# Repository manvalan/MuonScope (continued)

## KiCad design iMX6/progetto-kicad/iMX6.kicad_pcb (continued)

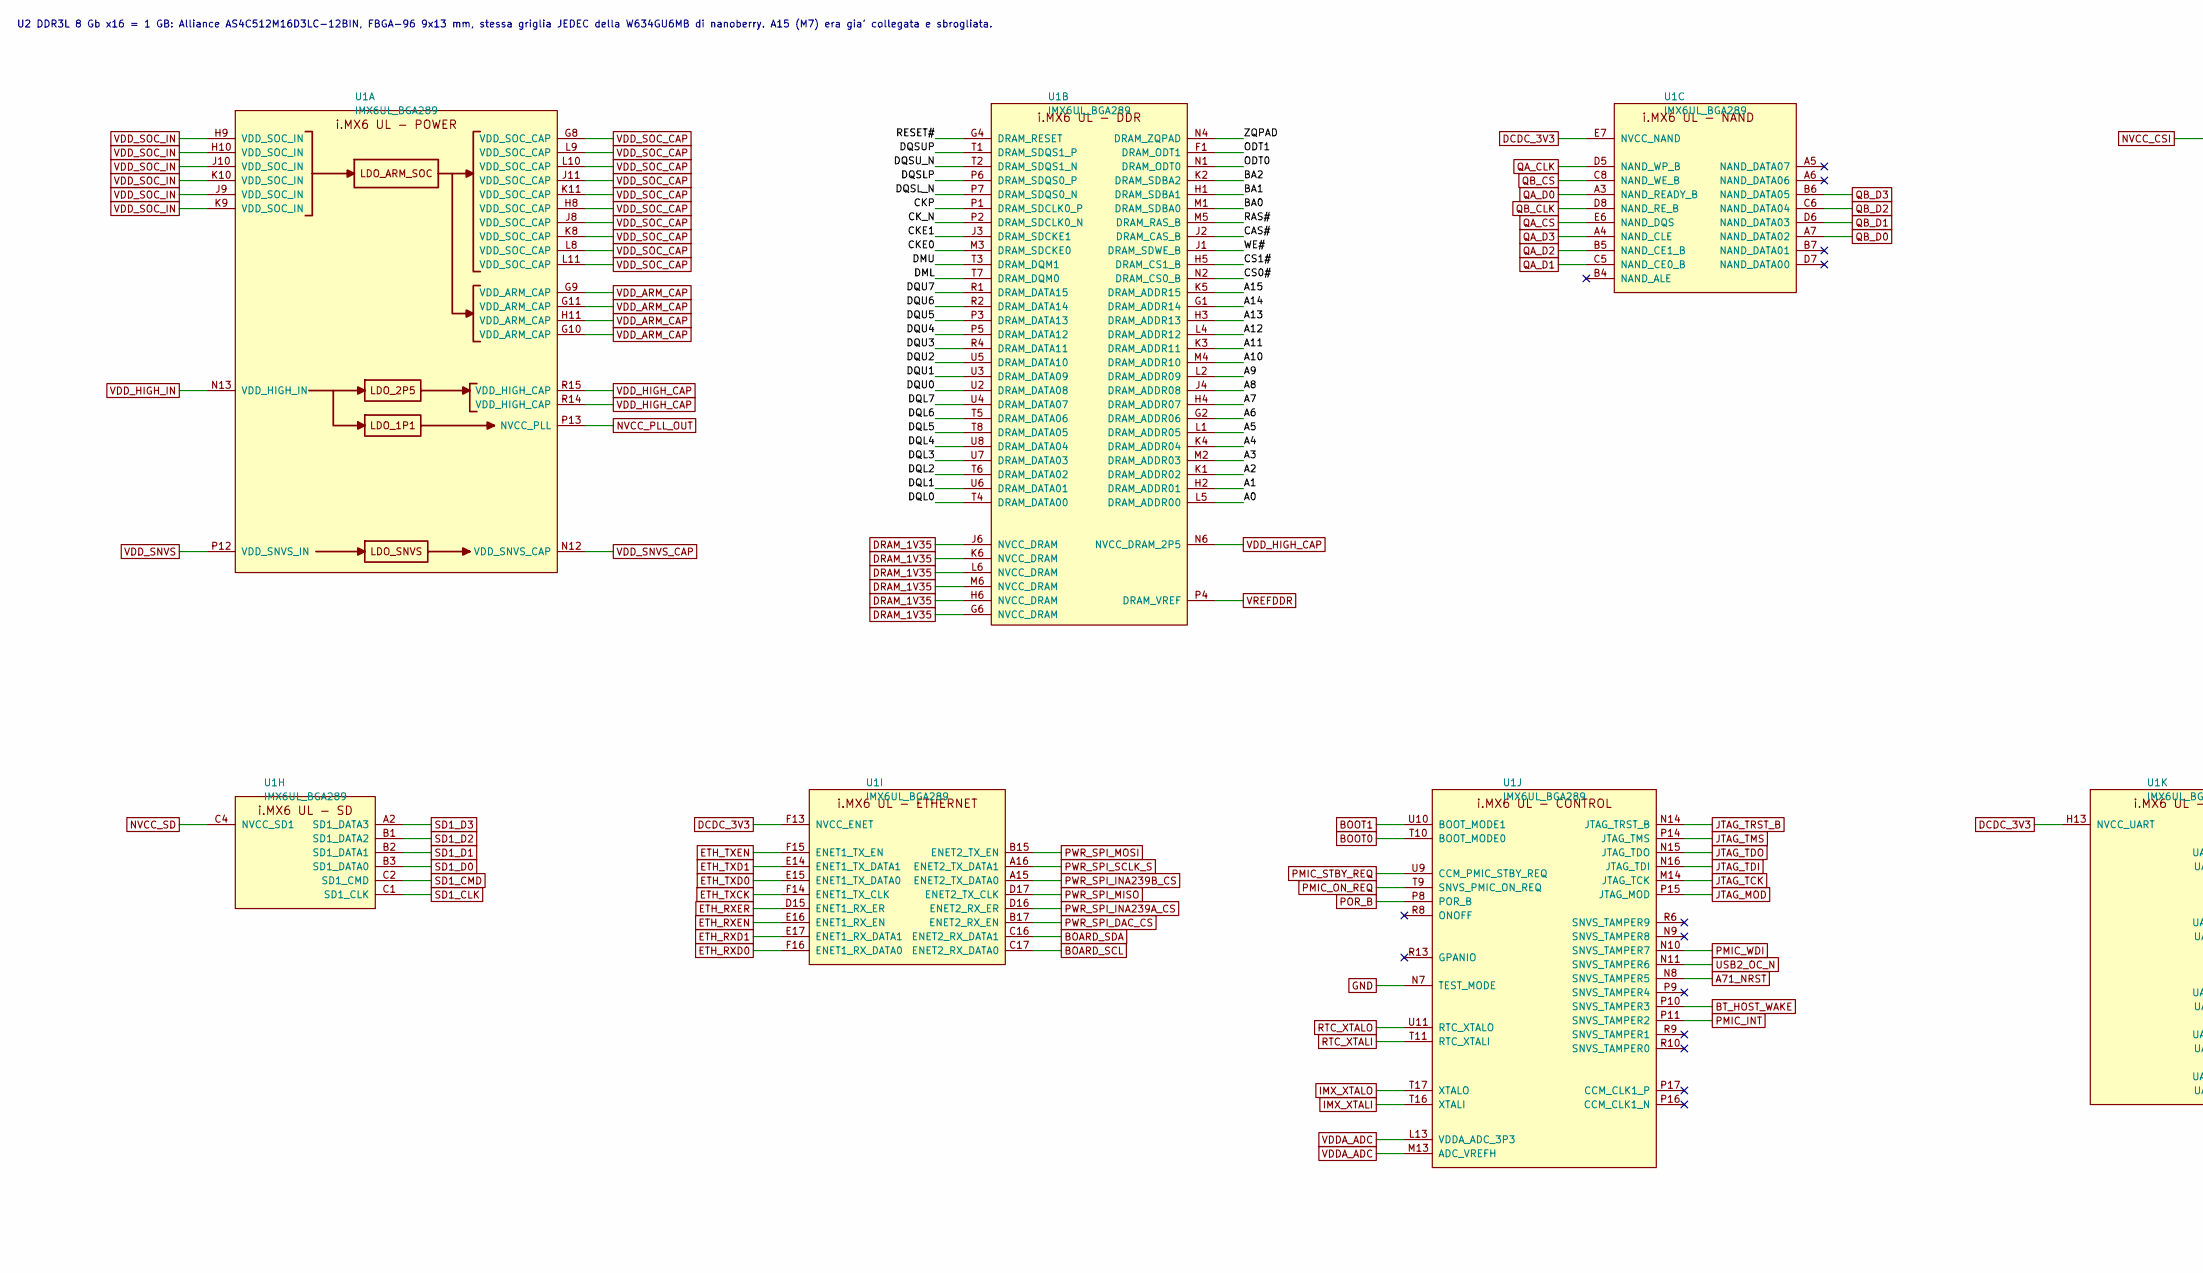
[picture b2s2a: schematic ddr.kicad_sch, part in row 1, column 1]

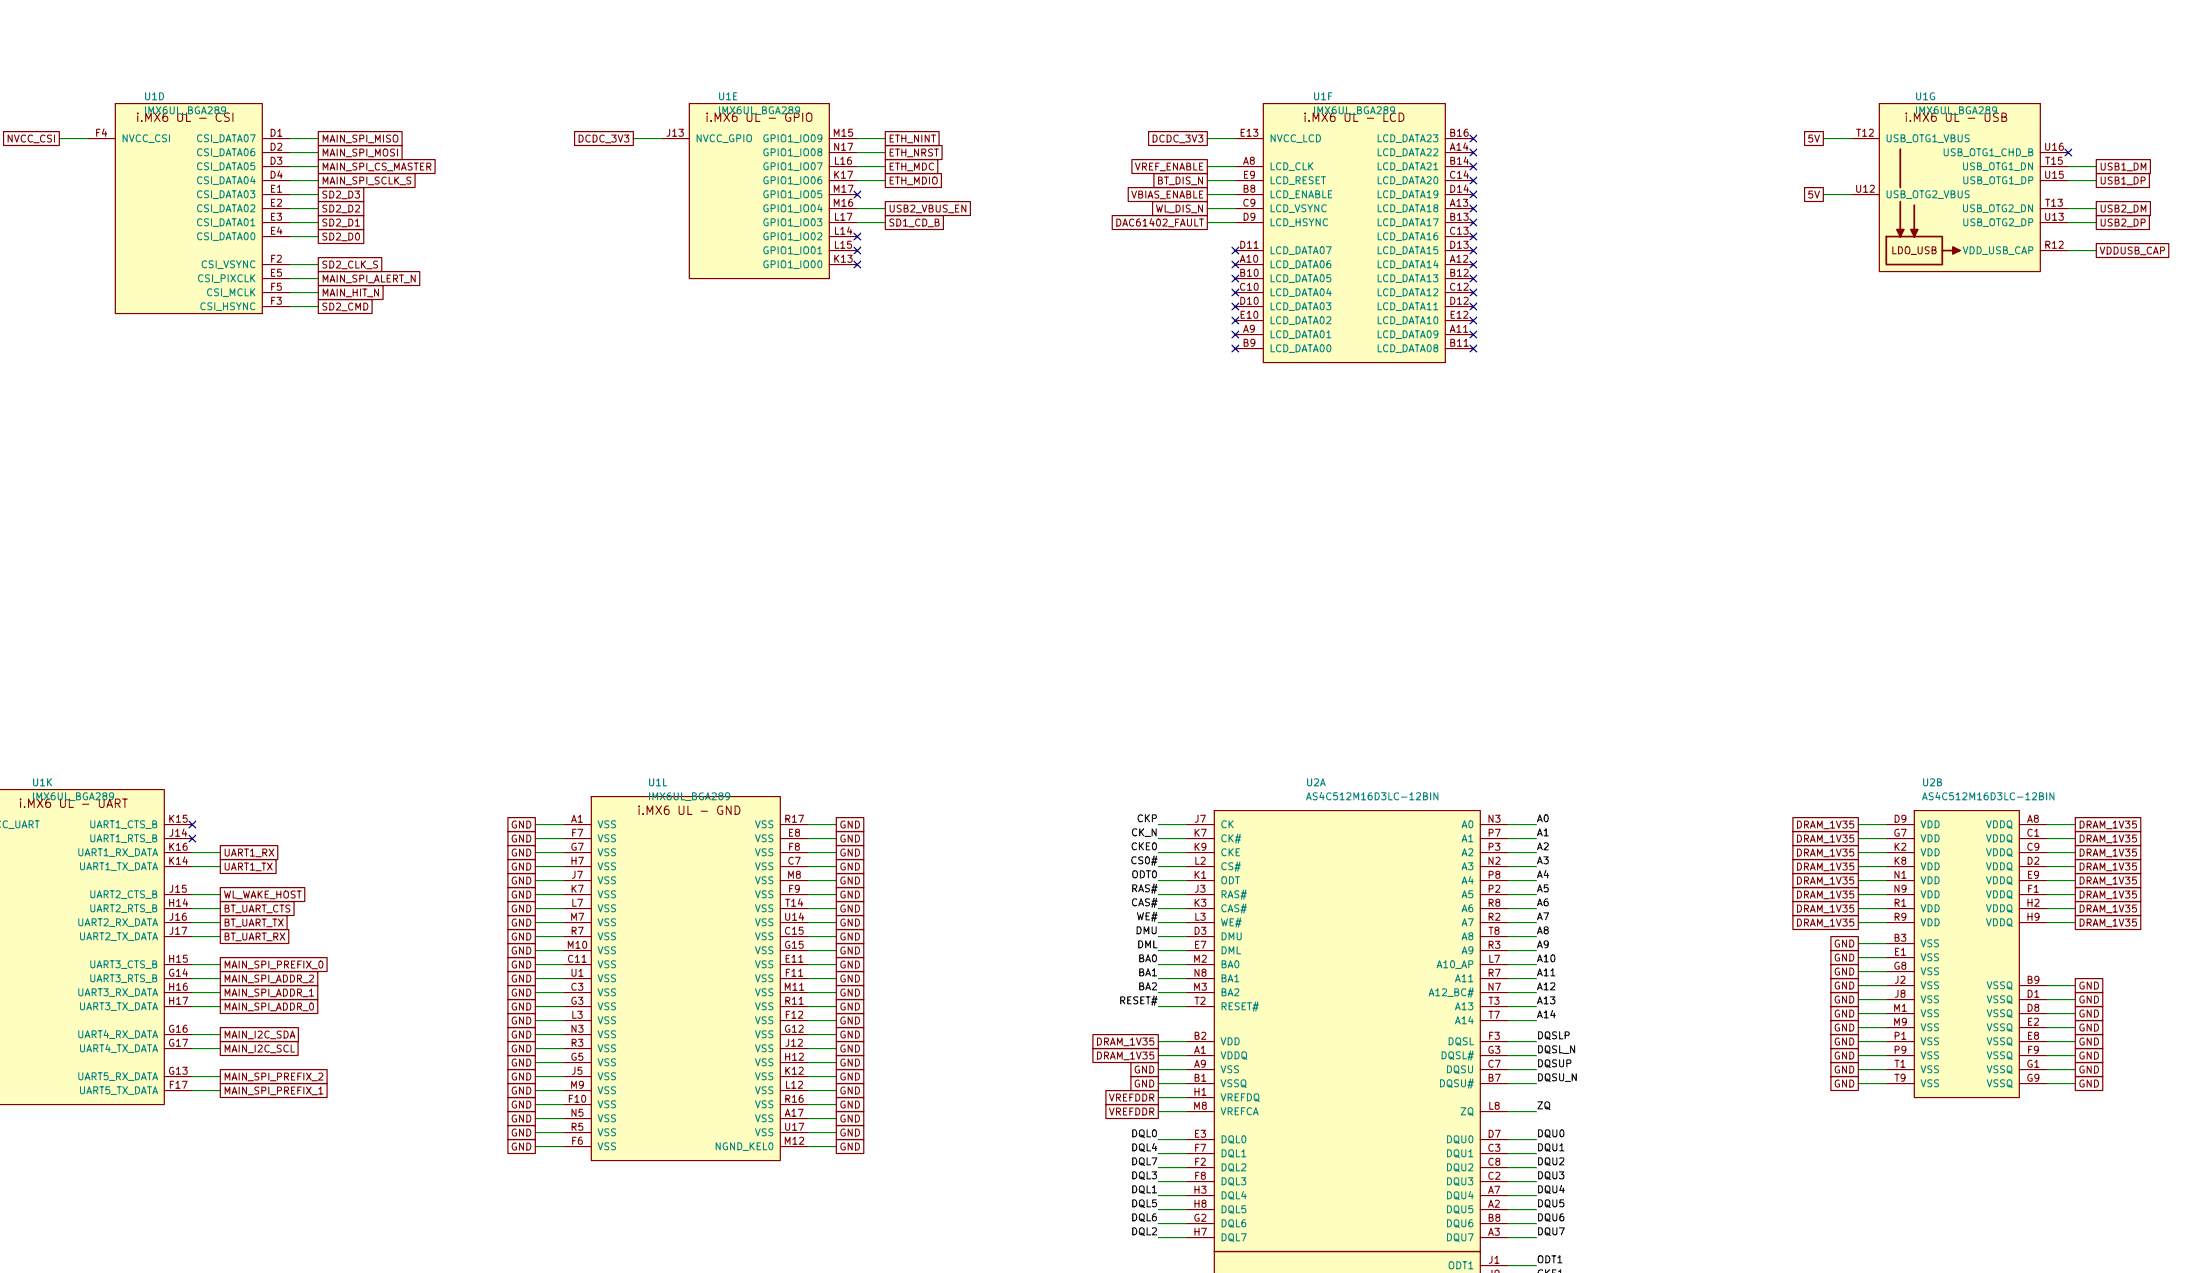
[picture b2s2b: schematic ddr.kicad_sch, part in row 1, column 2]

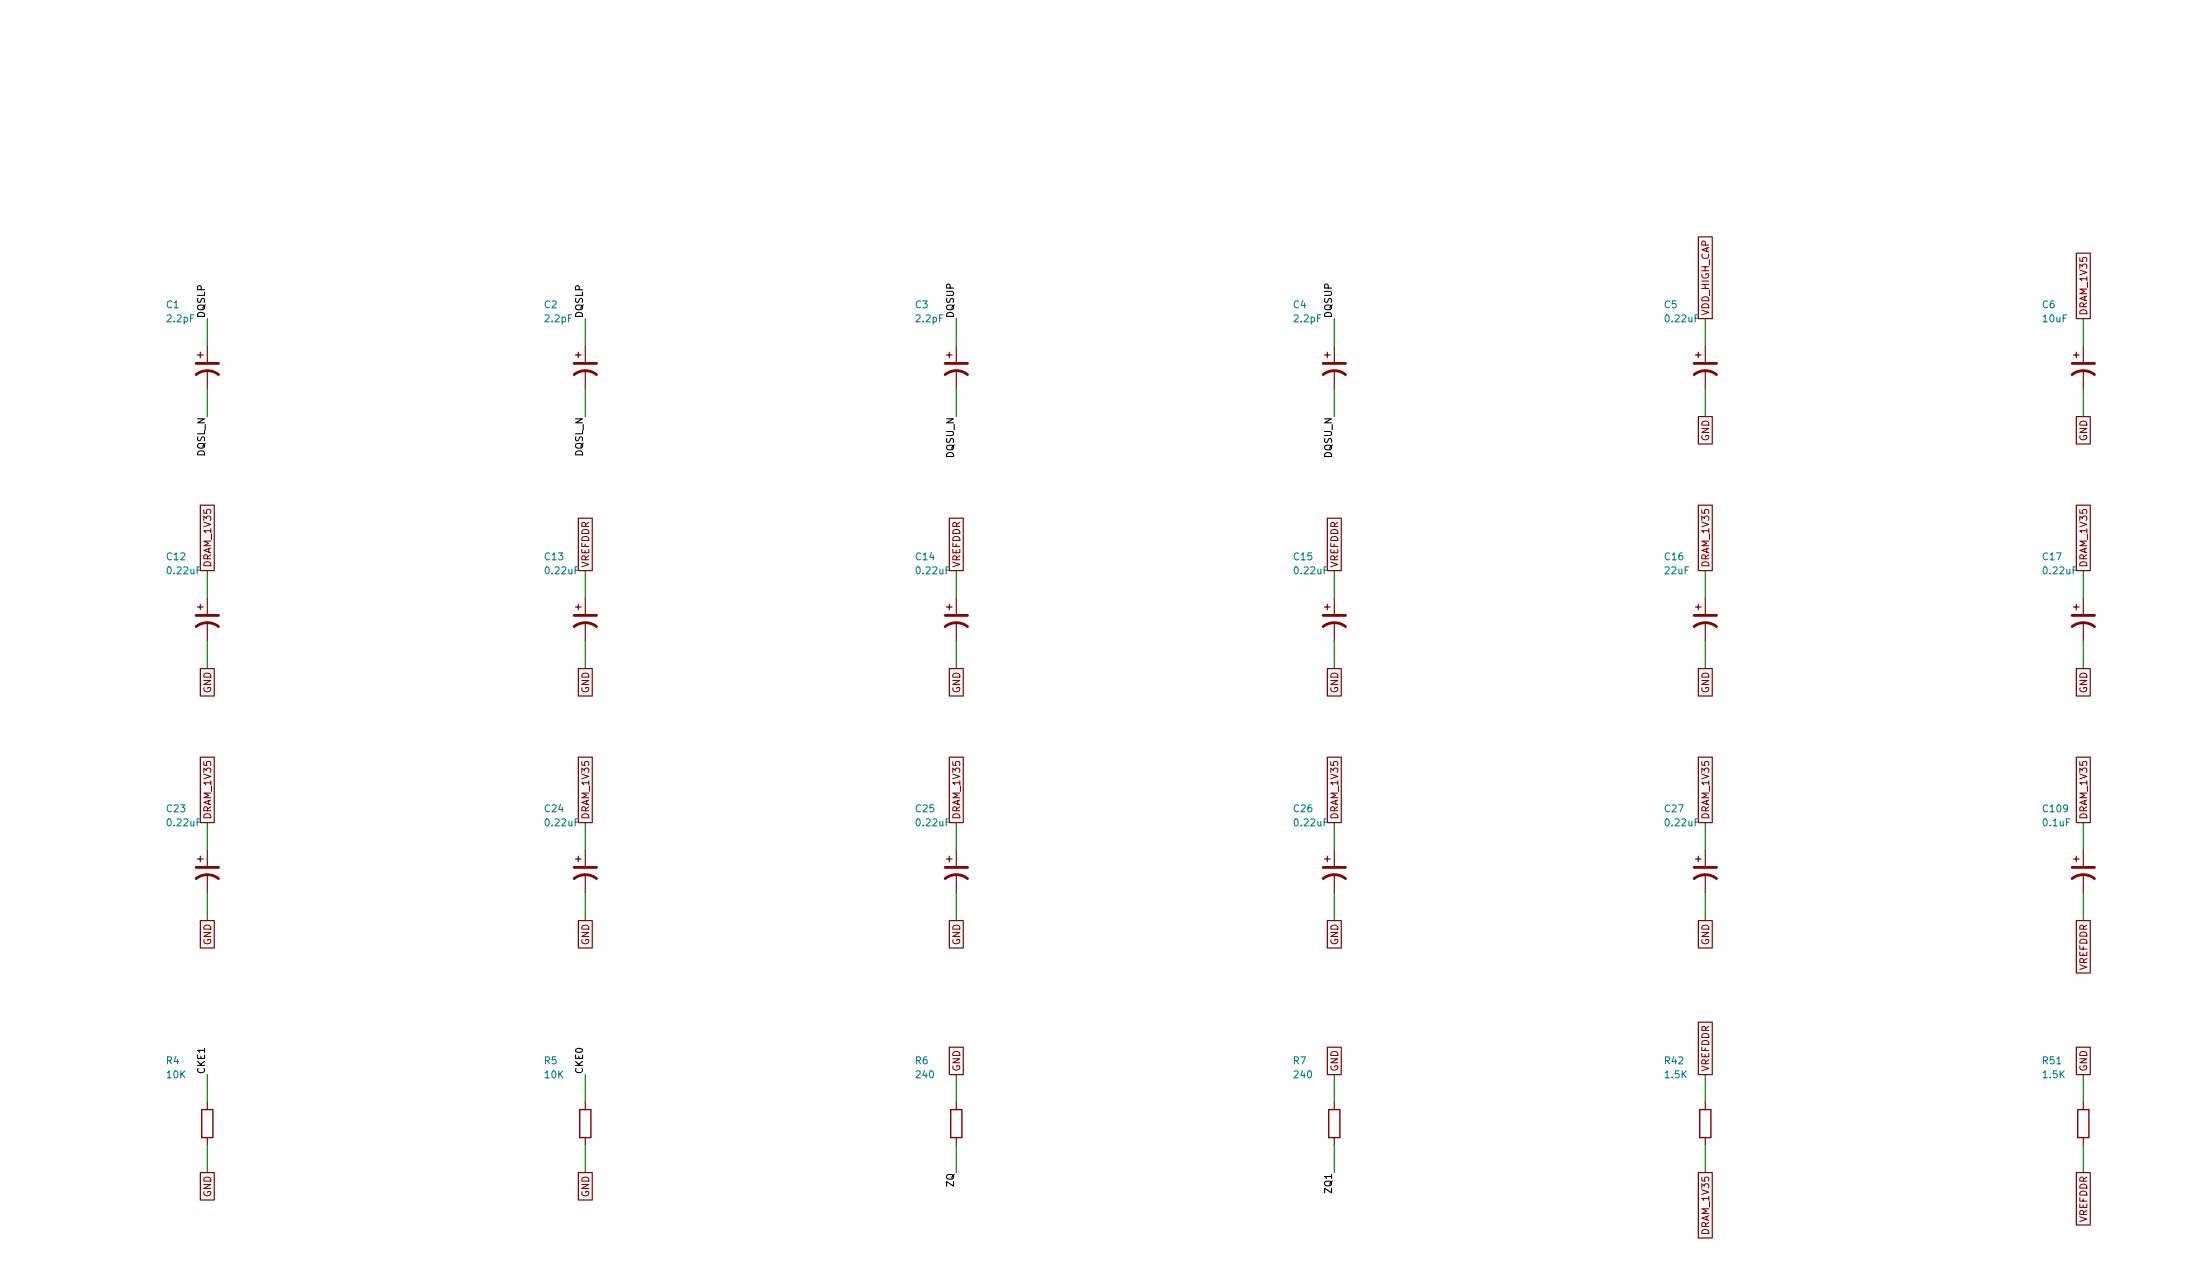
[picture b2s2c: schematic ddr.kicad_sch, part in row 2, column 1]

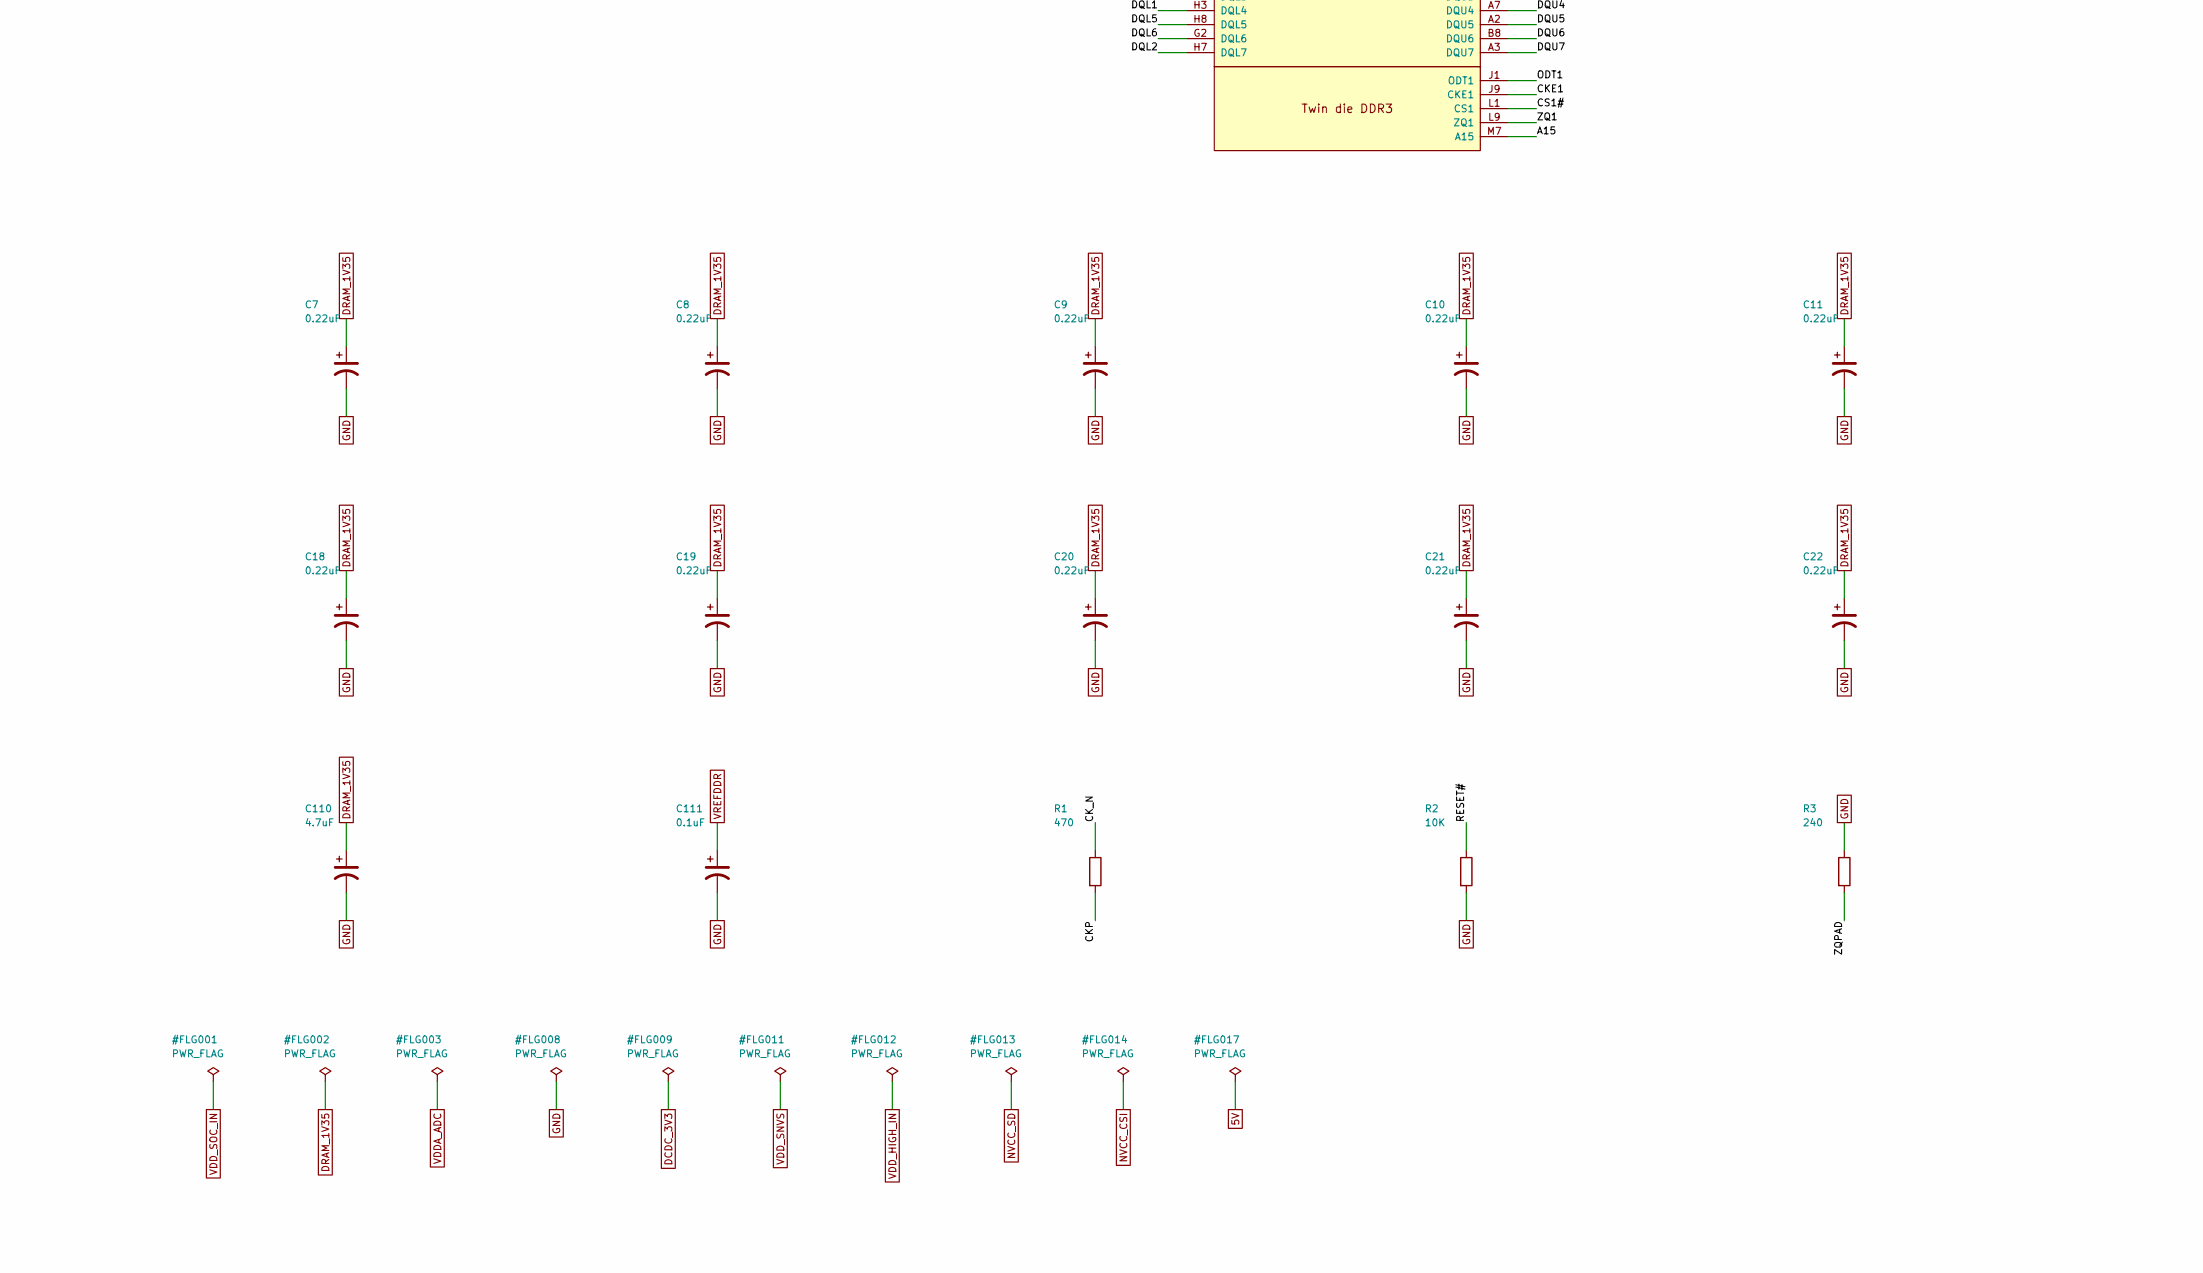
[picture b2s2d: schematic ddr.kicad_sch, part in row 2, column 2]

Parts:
C1, C2, C3, C4: 2.2pF; C_0402_narrow
C5, C7, C8, C9, C10, C11, C12, C13, C14, C15, C17, C18, C19, C20, C21, C22, C23, C24, C25, C26, C27: 0.22uF; C_0402_narrow
C6: 10uF; C_0603_narrow
C16: 22uF; C_0603_narrow
C109, C111: 0.1uF; C_0402_narrow
C110: 4.7uF; C_0402_narrow
R1: 470; R_0402_narrow
R2, R4, R5: 10K; R_0402_narrow
R3, R6, R7: 240; R_0402_narrow
R42, R51: 1.5K; R_0402_narrow
U1: IMX6UL_BGA289
U2: AS4C512M16D3LC-12BIN; DDR3_BGA96

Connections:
5V: U1.T12 (USB_OTG1_VBUS), U1.U12 (USB_OTG2_VBUS); also elsewhere on the board
/DDR3L/A0: U1.L5 (DRAM_ADDR00), U2.N3 (A0)
/DDR3L/A1: U1.H2 (DRAM_ADDR01), U2.P7 (A1)
/DDR3L/A2: U1.K1 (DRAM_ADDR02), U2.P3 (A2)
/DDR3L/A3: U1.M2 (DRAM_ADDR03), U2.N2 (A3)
/DDR3L/A4: U1.K4 (DRAM_ADDR04), U2.P8 (A4)
/DDR3L/A5: U1.L1 (DRAM_ADDR05), U2.P2 (A5)
/DDR3L/A6: U1.G2 (DRAM_ADDR06), U2.R8 (A6)
/DDR3L/A7: U1.H4 (DRAM_ADDR07), U2.R2 (A7)
/DDR3L/A8: U1.J4 (DRAM_ADDR08), U2.T8 (A8)
/DDR3L/A9: U1.L2 (DRAM_ADDR09), U2.R3 (A9)
/DDR3L/A10: U1.M4 (DRAM_ADDR10), U2.L7 (A10_AP)
/DDR3L/A11: U1.K3 (DRAM_ADDR11), U2.R7 (A11)
/DDR3L/A12: U1.L4 (DRAM_ADDR12), U2.N7 (A12_BC#)
/DDR3L/A13: U1.H3 (DRAM_ADDR13), U2.T3 (A13)
/DDR3L/A14: U1.G1 (DRAM_ADDR14), U2.T7 (A14)
/DDR3L/A15: U1.K5 (DRAM_ADDR15), U2.M7 (A15)
/DDR3L/BA0: U1.M1 (DRAM_SDBA0), U2.M2 (BA0)
/DDR3L/BA1: U1.H1 (DRAM_SDBA1), U2.N8 (BA1)
/DDR3L/BA2: U1.K2 (DRAM_SDBA2), U2.M3 (BA2)
/DDR3L/CAS#: U1.J2 (DRAM_CAS_B), U2.K3 (CAS#)
/DDR3L/CKE0: R5.1, U1.M3 (DRAM_SDCKE0), U2.K9 (CKE)
/DDR3L/CKE1: R4.1, U1.J3 (DRAM_SDCKE1), U2.J9 (CKE1)
/DDR3L/CKP: R1.2, U1.P1 (DRAM_SDCLK0_P), U2.J7 (CK)
/DDR3L/CK_N: R1.1, U1.P2 (DRAM_SDCLK0_N), U2.K7 (CK#)
/DDR3L/CS0#: U1.N2 (DRAM_CS0_B), U2.L2 (CS#)
/DDR3L/CS1#: U1.H5 (DRAM_CS1_B), U2.L1 (CS1)
/DDR3L/DML: U1.T7 (DRAM_DQM0), U2.E7 (DML)
/DDR3L/DMU: U1.T3 (DRAM_DQM1), U2.D3 (DMU)
/DDR3L/DQL0: U1.T4 (DRAM_DATA00), U2.E3 (DQL0)
/DDR3L/DQL1: U1.U6 (DRAM_DATA01), U2.H3 (DQL4)
/DDR3L/DQL2: U1.T6 (DRAM_DATA02), U2.H7 (DQL7)
/DDR3L/DQL3: U1.U7 (DRAM_DATA03), U2.F8 (DQL3)
/DDR3L/DQL4: U1.U8 (DRAM_DATA04), U2.F7 (DQL1)
/DDR3L/DQL5: U1.T8 (DRAM_DATA05), U2.H8 (DQL5)
/DDR3L/DQL6: U1.T5 (DRAM_DATA06), U2.G2 (DQL6)
/DDR3L/DQL7: U1.U4 (DRAM_DATA07), U2.F2 (DQL2)
/DDR3L/DQSLP: C1.1, C2.1, U1.P6 (DRAM_SDQS0_P), U2.F3 (DQSL)
/DDR3L/DQSL_N: C1.2, C2.2, U1.P7 (DRAM_SDQS0_N), U2.G3 (DQSL#)
/DDR3L/DQSUP: C3.1, C4.1, U1.T1 (DRAM_SDQS1_P), U2.C7 (DQSU)
/DDR3L/DQSU_N: C3.2, C4.2, U1.T2 (DRAM_SDQS1_N), U2.B7 (DQSU#)
/DDR3L/DQU0: U1.U2 (DRAM_DATA08), U2.D7 (DQU0)
/DDR3L/DQU1: U1.U3 (DRAM_DATA09), U2.C3 (DQU1)
/DDR3L/DQU2: U1.U5 (DRAM_DATA10), U2.C8 (DQU2)
/DDR3L/DQU3: U1.R4 (DRAM_DATA11), U2.C2 (DQU3)
/DDR3L/DQU4: U1.P5 (DRAM_DATA12), U2.A7 (DQU4)
/DDR3L/DQU5: U1.P3 (DRAM_DATA13), U2.A2 (DQU5)
/DDR3L/DQU6: U1.R2 (DRAM_DATA14), U2.B8 (DQU6)
/DDR3L/DQU7: U1.R1 (DRAM_DATA15), U2.A3 (DQU7)
/DDR3L/ODT0: U1.N1 (DRAM_ODT0), U2.K1 (ODT)
/DDR3L/ODT1: U1.F1 (DRAM_ODT1), U2.J1 (ODT1)
/DDR3L/RAS#: U1.M5 (DRAM_RAS_B), U2.J3 (RAS#)
/DDR3L/RESET#: R2.1, U1.G4 (DRAM_RESET), U2.T2 (RESET#)
/DDR3L/WE#: U1.J1 (DRAM_SDWE_B), U2.L3 (WE#)
/DDR3L/ZQ: R6.2, U2.L8 (ZQ)
/DDR3L/ZQ1: R7.2, U2.L9 (ZQ1)
/DDR3L/ZQPAD: R3.2, U1.N4 (DRAM_ZQPAD)
A71_NRST: U1.N8 (SNVS_TAMPER5); also elsewhere on the board
BOARD_SCL: U1.C17 (ENET2_RX_DATA0); also elsewhere on the board
BOARD_SDA: U1.C16 (ENET2_RX_DATA1); also elsewhere on the board
BOOT0: U1.T10 (BOOT_MODE0); also elsewhere on the board
BOOT1: U1.U10 (BOOT_MODE1); also elsewhere on the board
BT_DIS_N: U1.E9 (LCD_RESET); also elsewhere on the board
BT_HOST_WAKE: U1.P10 (SNVS_TAMPER3); also elsewhere on the board
BT_UART_CTS: U1.H14 (UART2_RTS_B); also elsewhere on the board
BT_UART_RX: U1.J17 (UART2_TX_DATA); also elsewhere on the board
BT_UART_TX: U1.J16 (UART2_RX_DATA); also elsewhere on the board
DAC61402_FAULT: U1.D9 (LCD_HSYNC); also elsewhere on the board
DCDC_3V3: U1.E7 (NVCC_NAND), U1.E13 (NVCC_LCD), U1.F13 (NVCC_ENET), U1.H13 (NVCC_UART), U1.J13 (NVCC_GPIO); also elsewhere on the board
DRAM_1V35: C6.1, C7.1, C8.1, C9.1, C10.1, C11.1, C12.1, C16.1, C17.1, C18.1, C19.1, C20.1, C21.1, C22.1, C23.1, C24.1, C25.1, C26.1, C27.1, C109.1, C110.1, R42.2, U1.G6 (NVCC_DRAM), U1.H6 (NVCC_DRAM), U1.J6 (NVCC_DRAM), U1.K6 (NVCC_DRAM), U1.L6 (NVCC_DRAM), U1.M6 (NVCC_DRAM), U2.A1 (VDDQ), U2.A8 (VDDQ), U2.B2 (VDD), U2.C1 (VDDQ), U2.C9 (VDDQ), U2.D2 (VDDQ), U2.D9 (VDD), U2.E9 (VDDQ), U2.F1 (VDDQ), U2.G7 (VDD), U2.H2 (VDDQ), U2.H9 (VDDQ), U2.K2 (VDD), U2.K8 (VDD), U2.N1 (VDD), U2.N9 (VDD), U2.R1 (VDD), U2.R9 (VDD); also elsewhere on the board
ETH_MDC: U1.L16 (GPIO1_IO07); also elsewhere on the board
ETH_MDIO: U1.K17 (GPIO1_IO06); also elsewhere on the board
ETH_NINT: U1.M15 (GPIO1_IO09); also elsewhere on the board
ETH_NRST: U1.N17 (GPIO1_IO08); also elsewhere on the board
ETH_RXD0: U1.F16 (ENET1_RX_DATA0); also elsewhere on the board
ETH_RXD1: U1.E17 (ENET1_RX_DATA1); also elsewhere on the board
ETH_RXEN: U1.E16 (ENET1_RX_EN); also elsewhere on the board
ETH_RXER: U1.D15 (ENET1_RX_ER); also elsewhere on the board
ETH_TXCK: U1.F14 (ENET1_TX_CLK); also elsewhere on the board
ETH_TXD0: U1.E15 (ENET1_TX_DATA0); also elsewhere on the board
ETH_TXD1: U1.E14 (ENET1_TX_DATA1); also elsewhere on the board
ETH_TXEN: U1.F15 (ENET1_TX_EN); also elsewhere on the board
GND: C5.2, C6.2, C7.2, C8.2, C9.2, C10.2, C11.2, C12.2, C13.2, C14.2, C15.2, C16.2, C17.2, C18.2, C19.2, C20.2, C21.2, C22.2, C23.2, C24.2, C25.2, C26.2, C27.2, C110.2, C111.2, R2.2, R3.1, R4.2, R5.2, R6.1, R7.1, R51.1, U1.A1 (VSS), U1.A17 (VSS), U1.C3 (VSS), U1.C7 (VSS), U1.C11 (VSS), U1.C15 (VSS), U1.E8 (VSS), U1.E11 (VSS), U1.F6 (VSS), U1.F7 (VSS), U1.F8 (VSS), U1.F9 (VSS), U1.F10 (VSS), U1.F11 (VSS), U1.F12 (VSS), U1.G3 (VSS), U1.G5 (VSS), U1.G7 (VSS), U1.G12 (VSS), U1.G15 (VSS), U1.H7 (VSS), U1.H12 (VSS), U1.J5 (VSS), U1.J7 (VSS), U1.J12 (VSS), U1.K7 (VSS), U1.K12 (VSS), U1.L3 (VSS), U1.L7 (VSS), U1.L12 (VSS), U1.M7 (VSS), U1.M8 (VSS), U1.M9 (VSS), U1.M10 (VSS), U1.M11 (VSS), U1.M12 (NGND_KEL0), U1.N3 (VSS), U1.N5 (VSS), U1.N7 (TEST_MODE), U1.R3 (VSS), U1.R5 (VSS), U1.R7 (VSS), U1.R11 (VSS), U1.R16 (VSS), U1.R17 (VSS), U1.T14 (VSS), U1.U1 (VSS), U1.U14 (VSS), U1.U17 (VSS), U2.A9 (VSS), U2.B1 (VSSQ), U2.B3 (VSS), U2.B9 (VSSQ), U2.D1 (VSSQ), U2.D8 (VSSQ), U2.E1 (VSS), U2.E2 (VSSQ), U2.E8 (VSSQ), U2.F9 (VSSQ), U2.G1 (VSSQ), U2.G8 (VSS), U2.G9 (VSSQ), U2.J2 (VSS), U2.J8 (VSS), U2.M1 (VSS), U2.M9 (VSS), U2.P1 (VSS), U2.P9 (VSS), U2.T1 (VSS), U2.T9 (VSS); also elsewhere on the board
IMX_XTALI: U1.T16 (XTALI); also elsewhere on the board
IMX_XTALO: U1.T17 (XTALO); also elsewhere on the board
JTAG_MOD: U1.P15 (JTAG_MOD); also elsewhere on the board
JTAG_TCK: U1.M14 (JTAG_TCK); also elsewhere on the board
JTAG_TDI: U1.N16 (JTAG_TDI); also elsewhere on the board
JTAG_TDO: U1.N15 (JTAG_TDO); also elsewhere on the board
JTAG_TMS: U1.P14 (JTAG_TMS); also elsewhere on the board
JTAG_TRST_B: U1.N14 (JTAG_TRST_B); also elsewhere on the board
MAIN_HIT_N: U1.F5 (CSI_MCLK); also elsewhere on the board
MAIN_I2C_SCL: U1.G17 (UART4_TX_DATA); also elsewhere on the board
MAIN_I2C_SDA: U1.G16 (UART4_RX_DATA); also elsewhere on the board
MAIN_SPI_ADDR_0: U1.H17 (UART3_TX_DATA); also elsewhere on the board
MAIN_SPI_ADDR_1: U1.H16 (UART3_RX_DATA); also elsewhere on the board
MAIN_SPI_ADDR_2: U1.G14 (UART3_RTS_B); also elsewhere on the board
MAIN_SPI_ALERT_N: U1.E5 (CSI_PIXCLK); also elsewhere on the board
MAIN_SPI_CS_MASTER: U1.D3 (CSI_DATA05); also elsewhere on the board
MAIN_SPI_MISO: U1.D1 (CSI_DATA07); also elsewhere on the board
MAIN_SPI_MOSI: U1.D2 (CSI_DATA06); also elsewhere on the board
MAIN_SPI_PREFIX_0: U1.H15 (UART3_CTS_B); also elsewhere on the board
MAIN_SPI_PREFIX_1: U1.F17 (UART5_TX_DATA); also elsewhere on the board
MAIN_SPI_PREFIX_2: U1.G13 (UART5_RX_DATA); also elsewhere on the board
MAIN_SPI_SCLK_S: U1.D4 (CSI_DATA04); also elsewhere on the board
NVCC_CSI: U1.F4 (NVCC_CSI); also elsewhere on the board
NVCC_PLL_OUT: U1.P13 (NVCC_PLL); also elsewhere on the board
NVCC_SD: U1.C4 (NVCC_SD1); also elsewhere on the board
PMIC_INT: U1.P11 (SNVS_TAMPER2); also elsewhere on the board
PMIC_ON_REQ: U1.T9 (SNVS_PMIC_ON_REQ); also elsewhere on the board
PMIC_STBY_REQ: U1.U9 (CCM_PMIC_STBY_REQ); also elsewhere on the board
PMIC_WDI: U1.N10 (SNVS_TAMPER7); also elsewhere on the board
POR_B: U1.P8 (POR_B); also elsewhere on the board
PWR_SPI_DAC_CS: U1.B17 (ENET2_RX_EN); also elsewhere on the board
PWR_SPI_INA239A_CS: U1.D16 (ENET2_RX_ER); also elsewhere on the board
PWR_SPI_INA239B_CS: U1.A15 (ENET2_TX_DATA0); also elsewhere on the board
PWR_SPI_MISO: U1.D17 (ENET2_TX_CLK); also elsewhere on the board
PWR_SPI_MOSI: U1.B15 (ENET2_TX_EN); also elsewhere on the board
PWR_SPI_SCLK_S: U1.A16 (ENET2_TX_DATA1); also elsewhere on the board
QA_CLK: U1.D5 (NAND_WP_B); also elsewhere on the board
QA_CS: U1.E6 (NAND_DQS); also elsewhere on the board
QA_D0: U1.A3 (NAND_READY_B); also elsewhere on the board
QA_D1: U1.C5 (NAND_CE0_B); also elsewhere on the board
QA_D2: U1.B5 (NAND_CE1_B); also elsewhere on the board
QA_D3: U1.A4 (NAND_CLE); also elsewhere on the board
QB_CLK: U1.D8 (NAND_RE_B); also elsewhere on the board
QB_CS: U1.C8 (NAND_WE_B); also elsewhere on the board
QB_D0: U1.A7 (NAND_DATA02); also elsewhere on the board
QB_D1: U1.D6 (NAND_DATA03); also elsewhere on the board
QB_D2: U1.C6 (NAND_DATA04); also elsewhere on the board
QB_D3: U1.B6 (NAND_DATA05); also elsewhere on the board
RTC_XTALI: U1.T11 (RTC_XTALI); also elsewhere on the board
RTC_XTALO: U1.U11 (RTC_XTALO); also elsewhere on the board
SD1_CD_B: U1.L17 (GPIO1_IO03); also elsewhere on the board
SD1_CLK: U1.C1 (SD1_CLK); also elsewhere on the board
SD1_CMD: U1.C2 (SD1_CMD); also elsewhere on the board
SD1_D0: U1.B3 (SD1_DATA0); also elsewhere on the board
SD1_D1: U1.B2 (SD1_DATA1); also elsewhere on the board
SD1_D2: U1.B1 (SD1_DATA2); also elsewhere on the board
SD1_D3: U1.A2 (SD1_DATA3); also elsewhere on the board
SD2_CLK_S: U1.F2 (CSI_VSYNC); also elsewhere on the board
SD2_CMD: U1.F3 (CSI_HSYNC); also elsewhere on the board
SD2_D0: U1.E4 (CSI_DATA00); also elsewhere on the board
SD2_D1: U1.E3 (CSI_DATA01); also elsewhere on the board
SD2_D2: U1.E2 (CSI_DATA02); also elsewhere on the board
SD2_D3: U1.E1 (CSI_DATA03); also elsewhere on the board
UART1_RX: U1.K16 (UART1_RX_DATA); also elsewhere on the board
UART1_TX: U1.K14 (UART1_TX_DATA); also elsewhere on the board
USB1_DM: U1.T15 (USB_OTG1_DN); also elsewhere on the board
USB1_DP: U1.U15 (USB_OTG1_DP); also elsewhere on the board
USB2_DM: U1.T13 (USB_OTG2_DN); also elsewhere on the board
USB2_DP: U1.U13 (USB_OTG2_DP); also elsewhere on the board
USB2_OC_N: U1.N11 (SNVS_TAMPER6); also elsewhere on the board
USB2_VBUS_EN: U1.M16 (GPIO1_IO04); also elsewhere on the board
VBIAS_ENABLE: U1.B8 (LCD_ENABLE); also elsewhere on the board
VDDA_ADC: U1.L13 (VDDA_ADC_3P3), U1.M13 (ADC_VREFH); also elsewhere on the board
VDDUSB_CAP: U1.R12 (VDD_USB_CAP); also elsewhere on the board
VDD_ARM_CAP: U1.G9 (VDD_ARM_CAP), U1.G10 (VDD_ARM_CAP), U1.G11 (VDD_ARM_CAP), U1.H11 (VDD_ARM_CAP); also elsewhere on the board
VDD_HIGH_CAP: C5.1, U1.N6 (NVCC_DRAM_2P5), U1.R14 (VDD_HIGH_CAP), U1.R15 (VDD_HIGH_CAP); also elsewhere on the board
VDD_HIGH_IN: U1.N13 (VDD_HIGH_IN); also elsewhere on the board
VDD_SNVS: U1.P12 (VDD_SNVS_IN); also elsewhere on the board
VDD_SNVS_CAP: U1.N12 (VDD_SNVS_CAP); also elsewhere on the board
VDD_SOC_CAP: U1.G8 (VDD_SOC_CAP), U1.H8 (VDD_SOC_CAP), U1.J8 (VDD_SOC_CAP), U1.J11 (VDD_SOC_CAP), U1.K8 (VDD_SOC_CAP), U1.K11 (VDD_SOC_CAP), U1.L8 (VDD_SOC_CAP), U1.L9 (VDD_SOC_CAP), U1.L10 (VDD_SOC_CAP), U1.L11 (VDD_SOC_CAP); also elsewhere on the board
VDD_SOC_IN: U1.H9 (VDD_SOC_IN), U1.H10 (VDD_SOC_IN), U1.J9 (VDD_SOC_IN), U1.J10 (VDD_SOC_IN), U1.K9 (VDD_SOC_IN), U1.K10 (VDD_SOC_IN); also elsewhere on the board
VREFDDR: C13.1, C14.1, C15.1, C109.2, C111.1, R42.1, R51.2, U1.P4 (DRAM_VREF), U2.H1 (VREFDQ), U2.M8 (VREFCA); also elsewhere on the board
VREF_ENABLE: U1.A8 (LCD_CLK); also elsewhere on the board
WL_DIS_N: U1.C9 (LCD_VSYNC); also elsewhere on the board
WL_WAKE_HOST: U1.J15 (UART2_CTS_B); also elsewhere on the board

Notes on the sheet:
U2 DDR3L 8 Gb x16 = 1 GB: Alliance AS4C512M16D3LC-12BIN, FBGA-96 9x13 mm, stessa griglia JEDEC della W634GU6MB di nanoberry. A15 (M7) era gia' collegata e sbrogliata.

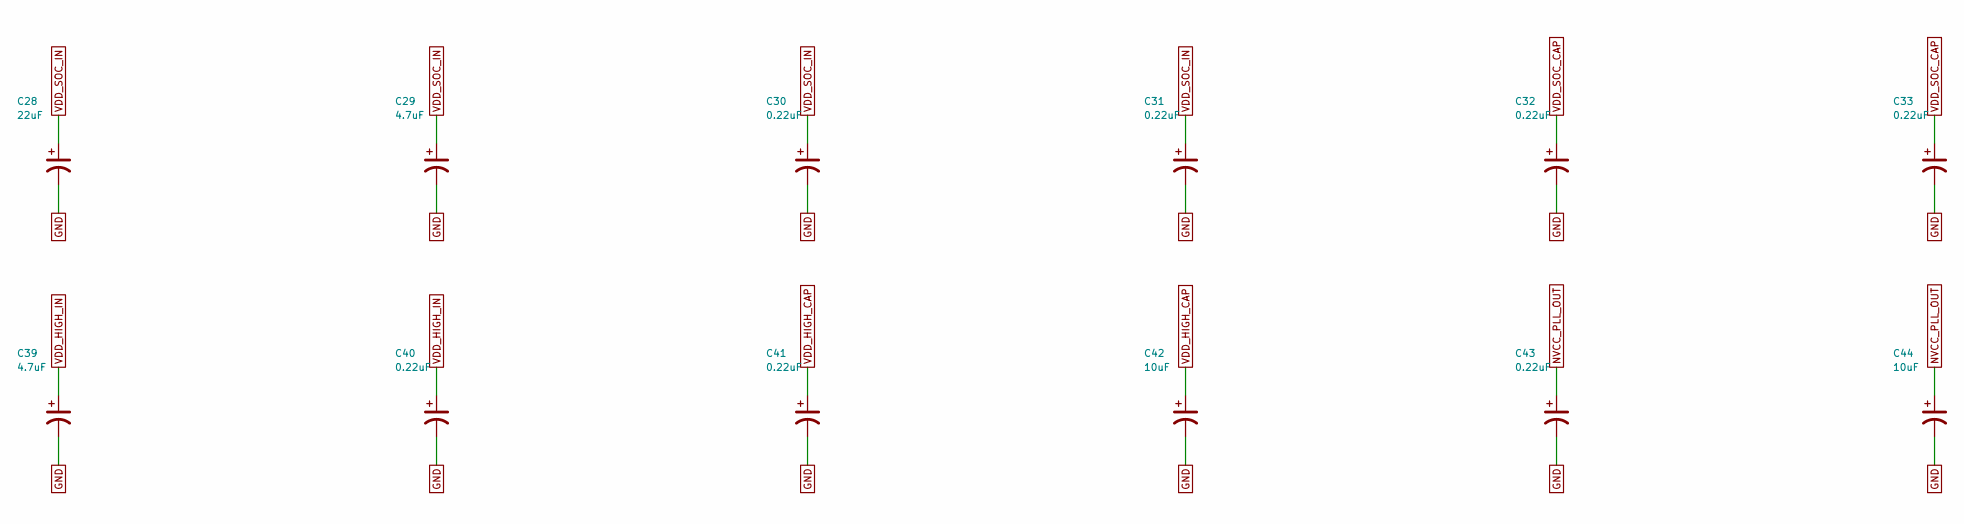
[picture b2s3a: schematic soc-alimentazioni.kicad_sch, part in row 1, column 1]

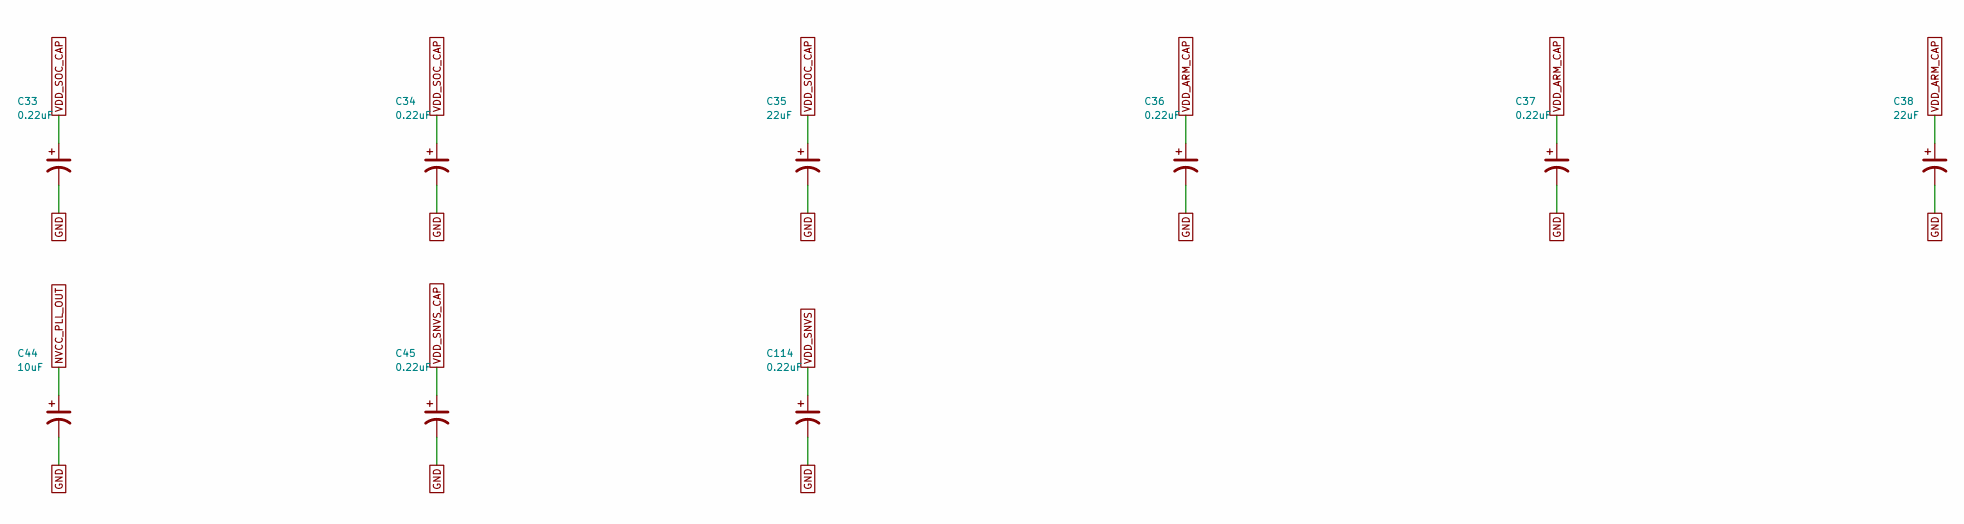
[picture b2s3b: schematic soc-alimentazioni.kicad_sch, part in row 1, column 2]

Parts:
C28, C35, C38: 22uF; C_0603_narrow
C29, C39: 4.7uF; C_0402_narrow
C30, C31, C32, C33, C34, C36, C37, C40, C41, C43, C45, C114: 0.22uF; C_0402_narrow
C42, C44: 10uF; C_0603_narrow

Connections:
GND: C28.2, C29.2, C30.2, C31.2, C32.2, C33.2, C34.2, C35.2, C36.2, C37.2, C38.2, C39.2, C40.2, C41.2, C42.2, C43.2, C44.2, C45.2, C114.2; also elsewhere on the board
NVCC_PLL_OUT: C43.1, C44.1; also elsewhere on the board
VDD_ARM_CAP: C36.1, C37.1, C38.1; also elsewhere on the board
VDD_HIGH_CAP: C41.1, C42.1; also elsewhere on the board
VDD_HIGH_IN: C39.1, C40.1; also elsewhere on the board
VDD_SNVS: C114.1; also elsewhere on the board
VDD_SNVS_CAP: C45.1; also elsewhere on the board
VDD_SOC_CAP: C32.1, C33.1, C34.1, C35.1; also elsewhere on the board
VDD_SOC_IN: C28.1, C29.1, C30.1, C31.1; also elsewhere on the board

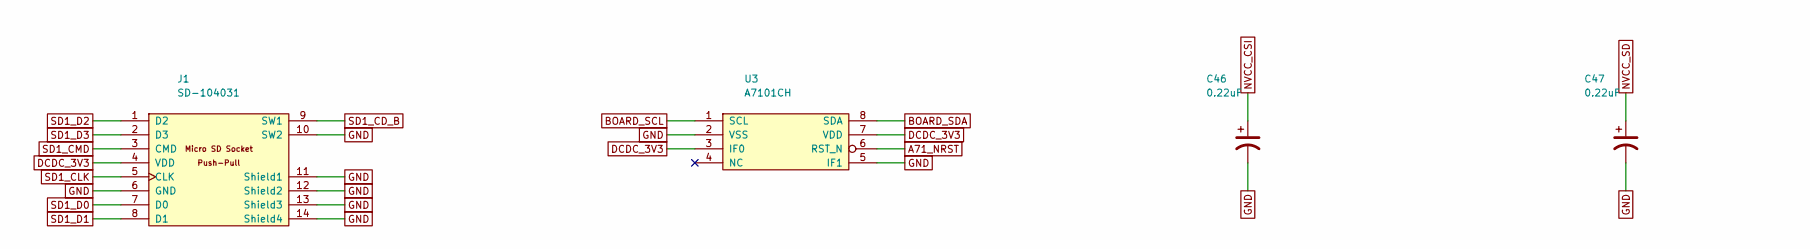
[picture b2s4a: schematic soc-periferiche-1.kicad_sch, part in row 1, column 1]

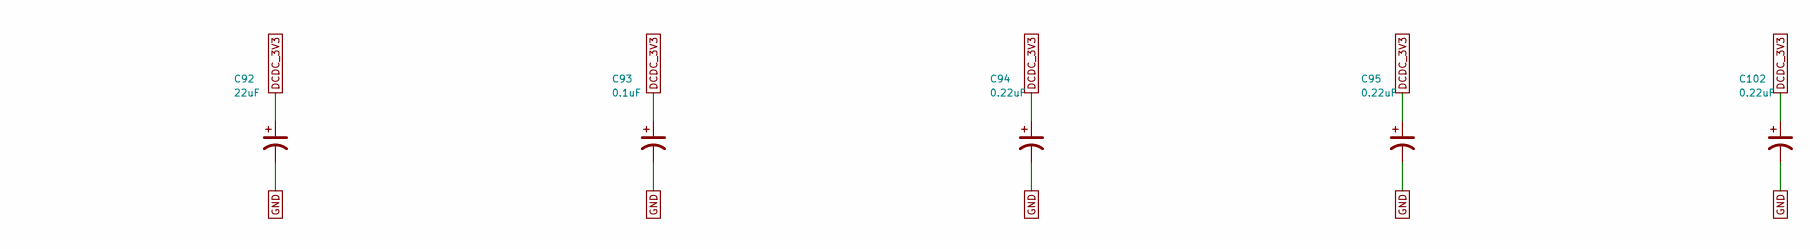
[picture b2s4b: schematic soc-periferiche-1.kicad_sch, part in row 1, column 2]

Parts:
C46, C47, C94, C95, C102: 0.22uF; C_0402_narrow
C92: 22uF; C_0603_narrow
C93: 0.1uF; C_0402_narrow
J1: SD-104031; uSD_104031
U3: A7101CH; SOT909-1

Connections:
A71_NRST: U3.6 (RST_N); also elsewhere on the board
BOARD_SCL: U3.1 (SCL); also elsewhere on the board
BOARD_SDA: U3.8 (SDA); also elsewhere on the board
DCDC_3V3: C92.1, C93.1, C94.1, C95.1, C102.1, J1.4 (VDD), U3.3 (IF0), U3.7 (VDD); also elsewhere on the board
GND: C46.2, C47.2, C92.2, C93.2, C94.2, C95.2, C102.2, J1.6 (GND), J1.10 (SW2), J1.11 (Shield1), J1.12 (Shield2), J1.13 (Shield3), J1.14 (Shield4), U3.2 (VSS), U3.5 (IF1); also elsewhere on the board
NVCC_CSI: C46.1; also elsewhere on the board
NVCC_SD: C47.1; also elsewhere on the board
SD1_CD_B: J1.9 (SW1); also elsewhere on the board
SD1_CLK: J1.5 (CLK); also elsewhere on the board
SD1_CMD: J1.3 (CMD); also elsewhere on the board
SD1_D0: J1.7 (D0); also elsewhere on the board
SD1_D1: J1.8 (D1); also elsewhere on the board
SD1_D2: J1.1 (D2); also elsewhere on the board
SD1_D3: J1.2 (D3); also elsewhere on the board
